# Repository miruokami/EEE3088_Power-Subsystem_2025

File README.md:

# EEE3088F 2025 Micro-Mouse Power Subsystem

Welcome to the repository for the **EEE3088F Micro-Mouse Power Subsystem Project**. This project focuses on designing and implementing a compact and efficient power module for a simplified micro-mouse robot. The goal is to meet all electrical and mechanical specifications, stay within a strict budget, and ensure seamless integration with the larger micro-mouse system.

## 👥 Team Members

- Student 1: SDZLIY001
- Student 2: CHGSHA008

## 📁 Repository Structure
```
> Power subsystem folder with 
  ├── gerbers / # Gerber files for PCB production
  ├── bom (PowerSchematic) / # Bill of Materials (.csv)
  ├── pos / # Pick-and-Place (PnP) files
  ├── screenshots / # Screenshots from JLCPCB uploads
  ├── schematics / # Final schematic file
  ├── pcb_layout 
```

## 🧠 Project Overview

This project involves designing the **power module** for the Micro-Mouse. The rest of the system — processor, sensing module, and motherboard — are pre-designed. The role is to design a subsystem that meets the power needs of the full system while adhering to design and budget constraints.

### Key Objectives

- Power 4 bidirectional motors (2x 200mA, 2x 500mA).
- Include battery monitoring with an INA219 over I2C.
- Implement dual-mode battery charging from a 9V input.
- Provide 3.3V (300mA) and 5V (1.5A) regulated outputs.
- Include external load switching (2x 1A High Side).
- Implement a low-power ON/OFF switch (<30µA OFF draw).
- Integrate USB-C (providing 9V out from USB host).
- Fit within 82x60mm PCB dimensions.
- Use correct JST and 2x16 connector footprints.

## 🛠️ Tools & Technologies

- **EDA Software**: EasyEDA / KiCAD / Altium (for PCB design)
- **Simulation**: LTSpice / MATLAB (optional)
- **PCB Manufacturer**: JLCPCB
- **Microcontroller**: STM32L476 (handled on separate processor board)
- **GitHub**: Version control and collaboration

## ✅ Requirements Summary

| Requirement | Description |
|-------------|-------------|
| Power Supply | 3V3 @ 300mA, 5V @ 1.5A |
| Charging | Dual-mode: 200mA and ~600mA |
| Battery Monitoring | INA219 on I2C |
| Motors | 2x 200mA, 2x 500mA |
| USB-C | Must provide 9V out |
| External Loads | 2x 1A, High-Side Switching |
| ON/OFF Switch | <30µA draw in OFF state |
| Budget | $35 per student (includes PCB + components) |

### 🛠️ PCB Ordering  
1. Upload `gerbers/*.zip` to JLCPCB.  
2. Use the provided `bom.csv` and `pos.csv` for assembly.  
3. Ensure components are in stock (check JLCPCB's inventory).
   
## 🧪 Testing Procedure

Testing will be performed using a standardised jig that validates:
- USB-C power output
- Battery charging behavior
- Regulated outputs (5V, 3.3V)
- Motor driver functionality
- INA219 battery monitoring
- ON/OFF switch behavior

## 🔗 Important Links

- [Veritasium Micro-Mouse Inspiration Video](https://www.youtube.com/watch?v=ZMQbHMgK2rw)
- [Micro Robotics Battery](https://www.robotics.org.za/802540)
- [JST Connector Specs](https://www.robotics.org.za/JST-PH-2P-90)
- [JLCPCB](https://jlcpcb.com

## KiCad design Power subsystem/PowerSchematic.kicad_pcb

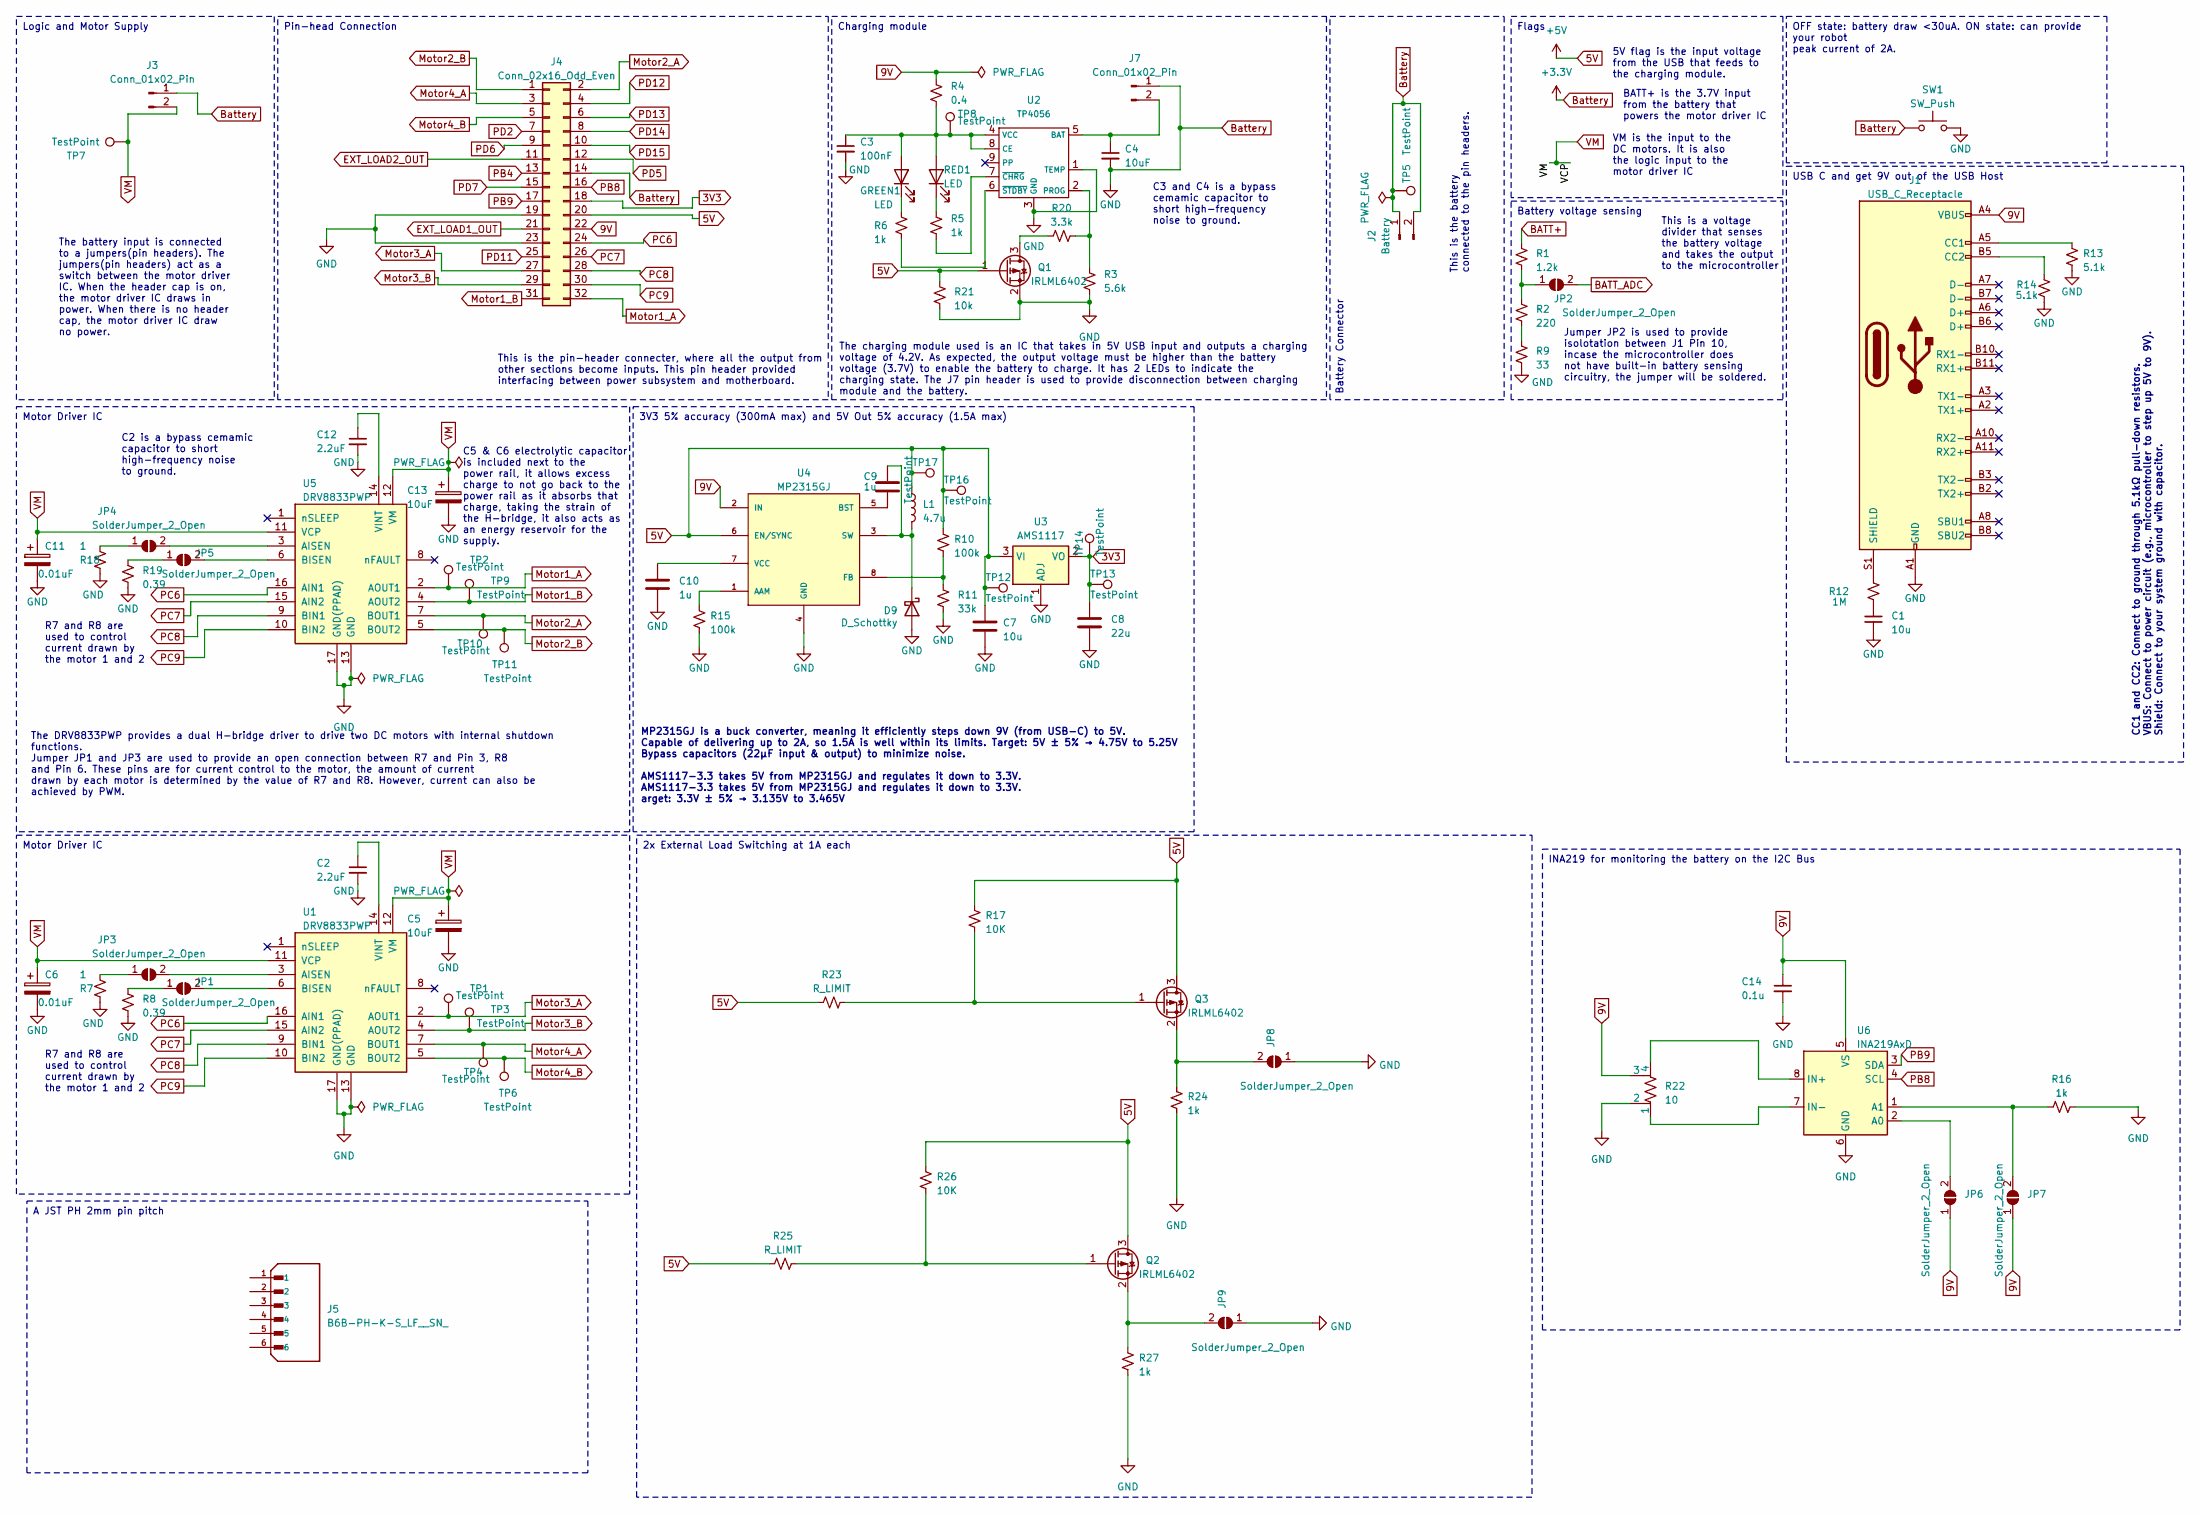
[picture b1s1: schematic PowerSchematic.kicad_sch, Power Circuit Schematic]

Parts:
C1, C7: 10u; C_0603_1608Metric
C2, C12: 2.2uF; C_0603_1608Metric
C3: 100nF; C_0603_1608Metric
C4, C13: 10uF; C_0603_1608Metric
C5: 10uF; CP_Elec_4x3
C6, C11: 0.01uF; CP_Elec_4x3
C8: 22u; C_0603_1608Metric
C9, C10: 1u; C_0603_1608Metric
C14: 0.1u; C_0603_1608Metric
D9: D_Schottky; D_2114_3652Metric
GREEN1: LED; LED_0201_0603Metric
J1: USB_C_Receptacle; USB_C_Receptacle_Amphenol_12401610E4-2A
J2: Battery; JST_PH_B2B-PH-K_1x02_P2.00mm_Vertical
J3, J7: Conn_01x02_Pin; PinHeader_1x02_P2.54mm_Vertical
J4: Conn_02x16_Odd_Even; PinHeader_2x16_P2.54mm_Horizontal
J5: B6B-PH-K-S_LF__SN_; PinHeader_1x06_P2.54mm_Horizontal; PARTREV N/A
JP1, JP2, JP3, JP4, JP5, JP6, JP7, JP8, JP9: SolderJumper_2_Open; SolderJumper-2_P1.3mm_Open_Pad1.0x1.5mm
L1: 4.7u; L_0201_0603Metric
Q1, Q2, Q3: IRLML6402; SOT-23
R1: 1.2k; R_0603_1608Metric
R2: 220; R_0603_1608Metric
R3: 5.6k; R_0603_1608Metric
R4: 0.4; R_0603_1608Metric
R5, R6, R16, R24, R27: 1k; R_0603_1608Metric
R7, R18: 1; R_0603_1608Metric
R8, R19: 0.39; R_0603_1608Metric
R9: 33; R_0603_1608Metric
R10, R15: 100k; R_0603_1608Metric
R11: 33k; R_0603_1608Metric
R12: 1M; R_0603_1608Metric
R13, R14: 5.1k; R_0603_1608Metric
R17, R26: 10K; R_0603_1608Metric
R20: 3.3k; R_0603_1608Metric
R21: 10k; R_0603_1608Metric
R22: 10; R_0603_1608Metric
R23, R25: R_LIMIT; R_0603_1608Metric
RED1: LED; LED_0201_0603Metric
SW1: SW_Push; Nidec_Copal_SH-7010A
TP1, TP2, TP3, TP4, TP5, TP6, TP7, TP8, TP9, TP10, TP11, TP12, TP13, TP14, TP16, TP17: TestPoint; TestPoint_Pad_1.0x1.0mm
U1, U5: DRV8833PWP; HTSSOP-16-1EP_4.4x5mm_P0.65mm_EP3.4x5mm_Mask2.46x2.31mm_The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
U2: TP4056; SOIC-8-1EP_3.9x4.9mm_P1.27mm_EP2.29x3mm
U3: AMS1117; SOT-223-3_TabPin2
U4: MP2315GJ; PinHeader_2x04_P2.54mm_Horizontal; MPN MP2315
U6: INA219AxD; SOIC-8_3.9x4.9mm_P1.27mm

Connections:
3V3: C8.1, J4.18, TP13.1, TP14.1, U3.2 (VO)
5V: C7.1, L1.1, Q1.1 (G), Q2.3 (D), Q3.3 (D), R10.1, R17.2, R21.1, R23.1, R25.1, R26.2, TP12.1, TP16.1, TP17.1, U3.3 (VI), U4.6 (EN/SYNC)
5V: J4.20
9V: C14.1, J1.A4 (VBUS), J1.A9 (VBUS), J1.B4 (VBUS), J1.B9 (VBUS), J4.22, JP6.1 (A), JP7.1 (A), R4.2, R22.3, U4.2 (IN), U6.5 (VS)
BATT+: R1.1
BATT_ADC: JP2.2 (B)
Battery: C1.2, C2.2, C3.2, C4.2, C5.2, C6.2, C7.2, C8.2, C10.2, C11.2, C12.2, C13.2, C14.2, D9.2 (A), J1.A1 (GND), J1.A12 (GND), J1.B1 (GND), J1.B12 (GND), J2.1, J2.2, J3.1, J4.14, J4.19, J4.23, J7.1, JP8.1 (A), JP9.1 (A), Q1.2 (S), R3.2, R7.2, R8.2, R9.2, R11.2, R13.2, R14.2, R15.2, R16.2, R18.2, R19.2, R21.2, R22.2, R24.1, R27.1, SW1.1, SW1.2, TP5.1, U1.13 (GND), U1.17 (GND(PPAD)), U2.1 (TEMP), U2.3 (GND), U3.1 (ADJ), U4.4 (GND), U5.13 (GND), U5.17 (GND(PPAD)), U6.6 (GND)
EXT_LOAD1_OUT: J4.21
EXT_LOAD2_OUT: J4.11
Motor1_A: J4.32, TP2.1, U5.2 (AOUT1)
Motor1_B: J4.31, TP9.1, U5.4 (AOUT2)
Motor2_A: J4.2, TP10.1, U5.7 (BOUT1)
Motor2_B: J4.1, TP11.1, U5.5 (BOUT2)
Motor3_A: J4.27, TP1.1, U1.2 (AOUT1)
Motor3_B: J4.29, TP3.1, U1.4 (AOUT2)
Motor4_A: J4.3, TP4.1, U1.7 (BOUT1)
Motor4_B: J4.5, TP6.1, U1.5 (BOUT2)
unnamed: C1.1, R12.2
unnamed: C9.1, D9.1 (K), L1.2, U4.3 (SW)
unnamed: C3.1, GREEN1.2 (A), R4.1, RED1.2 (A), TP8.1, U2.4 (VCC), U2.8 (CE)
unnamed: GREEN1.1 (K), R6.2
unnamed: J1.A5 (CC1), R13.1
unnamed: J1.B5 (CC2), R14.1
unnamed: J1.S1 (SHIELD), R12.1
unnamed: C4.1, J7.2, U2.5 (BAT)
unnamed: JP1.1 (A), R8.1
unnamed: JP1.2 (B), U1.6 (BISEN)
unnamed: JP2.1 (A), R1.2, R2.1
unnamed: JP3.1 (A), R7.1
unnamed: JP3.2 (B), U1.3 (AISEN)
unnamed: JP4.1 (A), R18.1
unnamed: JP4.2 (B), U5.3 (AISEN)
unnamed: JP5.1 (A), R19.1
unnamed: JP5.2 (B), U5.6 (BISEN)
unnamed: JP6.2 (B), U6.2 (A0)
unnamed: JP7.2 (B), R16.1, U6.1 (A1)
unnamed: JP8.2 (B), Q3.2 (S), R24.2
unnamed: JP9.2 (B), Q2.2 (S), R27.2
unnamed: Q1.3 (D), R20.1
unnamed: Q2.1 (G), R25.2, R26.1
unnamed: Q3.1 (G), R17.1, R23.2
unnamed: R2.2, R9.1
unnamed: R5.2, RED1.1 (K)
unnamed: C2.1, U1.14 (VINT)
unnamed: R3.1, R20.2, U2.2 (PROG)
unnamed: R5.1, U2.7 (~CHRG)
unnamed: R6.1, U2.6 (~STDBY)
unnamed: R15.1, U4.1 (AAM)
unnamed: C9.2, U4.5 (BST)
unnamed: R10.2, R11.1, U4.8 (FB)
unnamed: C10.1, U4.7 (VCC)
unnamed: C12.1, U5.14 (VINT)
unnamed: R22.4, U6.8 (IN+)
unnamed: R22.1, U6.7 (IN-)
PB4: J4.13
PB8: J4.16, U6.4 (SCL)
PB9: J4.17, U6.3 (SDA)
PC6: J4.24, U1.16 (AIN1), U5.16 (AIN1)
PC7: J4.26, U1.15 (AIN2), U5.15 (AIN2)
PC8: J4.28, U1.9 (BIN1), U5.9 (BIN1)
PC9: J4.30, U1.10 (BIN2), U5.10 (BIN2)
PD2: J4.7
PD5: J4.12
PD6: J4.9
PD7: J4.15
PD11: J4.25
PD12: J4.4
PD13: J4.6
PD14: J4.8
PD15: J4.10
VM: C5.1, C6.1, C11.1, C13.1, J3.2, TP7.1, U1.11 (VCP), U1.12 (VM), U5.11 (VCP), U5.12 (VM)

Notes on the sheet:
Flags
INA219 for monitoring the battery on the I2C Bus
Motor Driver IC
USB C and get 9V out of the USB Host
Battery voltage sensing
3V3 5% accuracy (300mA max) and 5V Out 5% accuracy (1.5A max)
OFF state: battery draw <30uA. ON state: can provide your robot peak current of 2A.
Battery Connector
2x External Load Switching at 1A each
A JST PH 2mm pin pitch
Pin-head Connection
Charging module
Logic and Motor Supply
The charging module used is an IC that takes in 5V USB input and outputs a charging voltage of 4.2V. As expected, the output voltage must be higher than the battery voltage (3.7V) to enable the battery to charge. It has 2 LEDs to indicate the charging state. The J7 pin header is used to provide dis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
This is the pin-header connecter, where all the output from other sections become inputs. This pin header provided interfacing between power subsystem and motherboard.
BATT+ is the 3.7V input from the battery that powers the motor driver IC
C2 is a bypass cemamic capacitor to short high-frequency noise to ground.
R7 and R8 are used to control current drawn by the motor 1 and 2
This is a voltage divider that senses the battery voltage and takes the output to the microcontroller
The battery input is connected to a jumpers(pin headers). The jumpers(pin headers) act as a switch between the motor driver IC. When the header cap is on, the motor driver IC draws in power. When there is no header cap, the motor driver IC draw no power.
C3 and C4 is a bypass cemamic capacitor to short high-frequency noise to ground.
CC1 and CC2: Connect to ground through 5.1kΩ pull-down resistors. VBUS: Connect to power circuit (e.g., microcontroller to step up 5V to 9V). Shield: Connect to your system ground with capacitor.
The DRV8833PWP provides a dual H-bridge driver to drive two DC motors with internal shutdown functions. Jumper JP1 and JP3 are used to provide an open connection between R7 and Pin 3, R8 and Pin 6. These pins are for current control to the motor, the amount of current drawn by each motor is determi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
C5 & C6 electrolytic capacitor is included next to the power rail, it allows excess charge to not go back to the power rail as it absorbs that charge, taking the strain of the H-bridge, it also acts as an energy reservoir for the supply.
This is the battery connected to the pin headers.
MP2315GJ is a buck converter, meaning it efficiently steps down 9V (from USB-C) to 5V. Capable of delivering up to 2A, so 1.5A is well within its limits. Target: 5V ± 5% → 4.75V to 5.25V Bypass capacitors (22µF input & output) to minimize noise. AMS1117-3.3 takes 5V from MP2315GJ and regulates it d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
Jumper JP2 is used to provide isolotation between J1 Pin 10, incase the microcontroller does not have built-in battery sensing circuitry, the jumper will be soldered.
5V flag is the input voltage from the USB that feeds to the charging module.
VM is the input to the DC motors. It is also the logic input to the motor driver IC

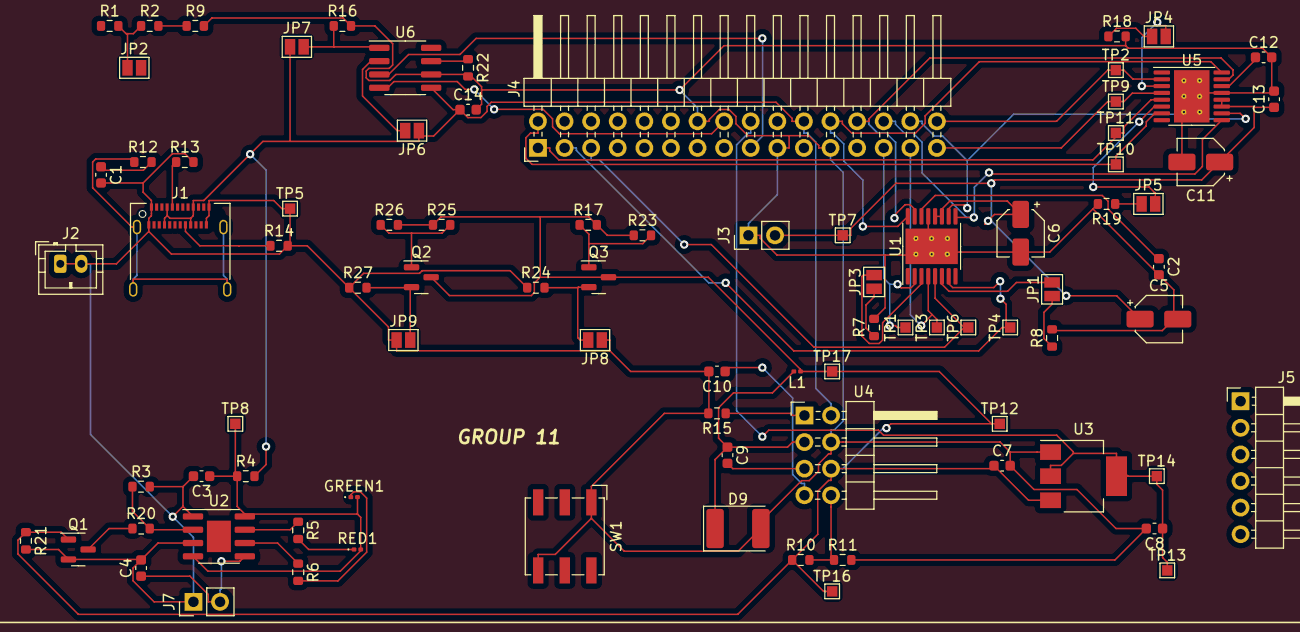
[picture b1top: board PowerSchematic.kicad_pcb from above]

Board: 2 copper layers, 86 parts (0 on the bottom side), 55 nets.

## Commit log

2025-04-24 Added project files via upload
2025-04-24 Update README.md to be more readable
2025-04-24 redefined README.md
